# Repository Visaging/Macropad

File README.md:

# Hackpad

## Softwares Used
* Autodesk Fusion
* Kicad 9.0

## BOM
* **Microcontroller** - Seeed Studio XIAO RP2040
* **Switches(x6)** - Cherry MX Compatible Mechanical Switches
* **Keycaps(x6)** - Blank DSA Keycaps
* **RGB LED(x4)** - SK6812MINI Addressable RGB LED(s)
* **OLED Display(x1)** - SSD1306 128x32 OLED Display
* **Bolts:** M3x16 Bolt(x4)
* **Heatset:** M3 Heatset(x4)
* **Case** - 3D printed

## PCB Layout
* **Key Pins:** D0, D1, D3, D6, D7, D8
* **RGB:** D10
* **OLED**: D5, D6, 3V3
* **Power:** VBUS (5V)

## PCB Schematic and Design

## Case Model

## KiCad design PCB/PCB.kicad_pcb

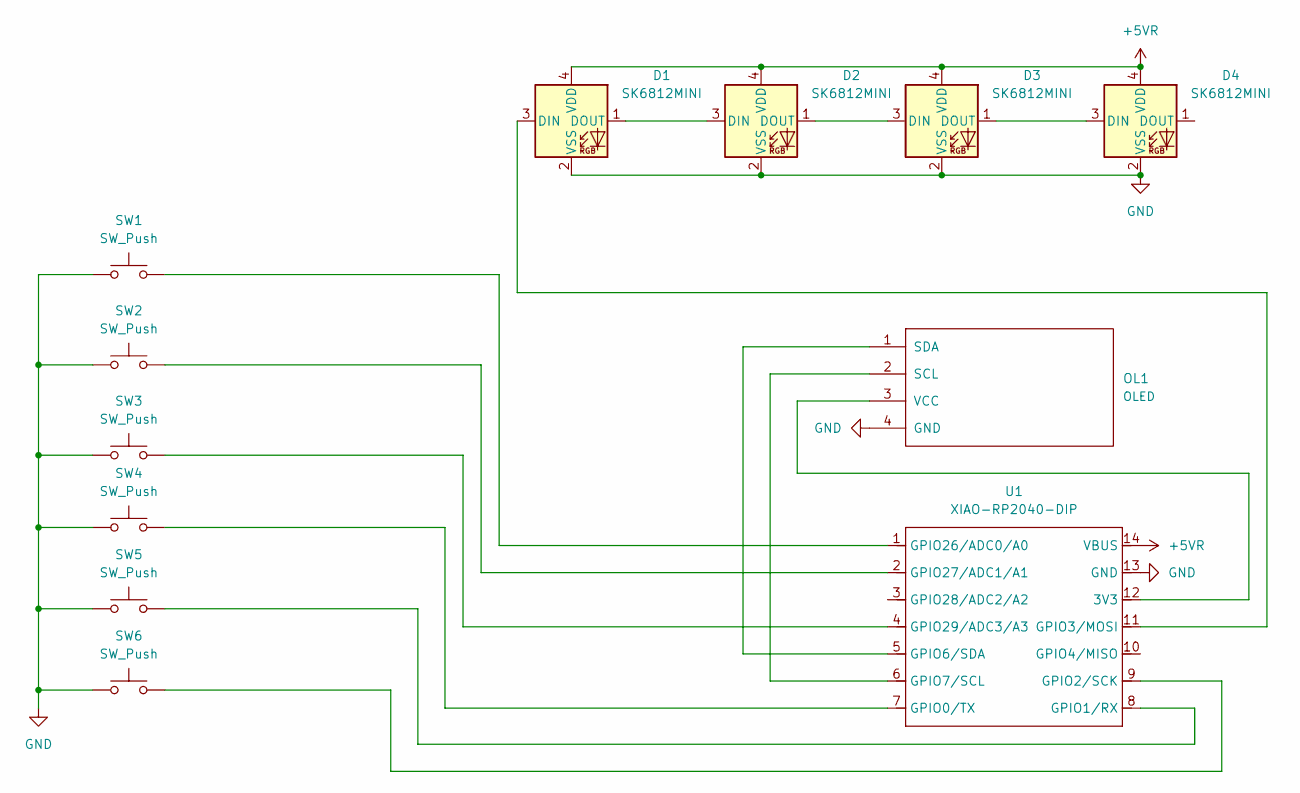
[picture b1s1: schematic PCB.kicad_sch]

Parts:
D1, D2, D3, D4: SK6812MINI; LED_SK6812MINI_PLCC4_3.5x3.5mm_P1.75mm
OL1: OLED
SW1, SW2, SW3, SW4, SW5, SW6: SW_Push; SW_Cherry_MX_1.00u_PCB
U1: XIAO-RP2040-DIP

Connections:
+5VR: D1.4 (VDD), D2.4 (VDD), D3.4 (VDD), D4.4 (VDD), U1.14 (VBUS)
GND: D1.2 (VSS), D2.2 (VSS), D3.2 (VSS), D4.2 (VSS), OL1.4 (GND), SW1.1, SW2.1, SW3.1, SW4.1, SW5.1, SW6.1, U1.13 (GND)
unnamed: D1.3 (DIN), U1.11 (GPIO3/MOSI)
unnamed: D1.1 (DOUT), D2.3 (DIN)
unnamed: D2.1 (DOUT), D3.3 (DIN)
unnamed: D3.1 (DOUT), D4.3 (DIN)
unnamed: OL1.2 (SCL), U1.6 (GPIO7/SCL)
unnamed: OL1.1 (SDA), U1.5 (GPIO6/SDA)
unnamed: OL1.3 (VCC), U1.12 (3V3)
unnamed: SW4.2, U1.7 (GPIO0/TX)
unnamed: SW5.2, U1.8 (GPIO1/RX)
unnamed: SW6.2, U1.9 (GPIO2/SCK)
unnamed: SW1.2, U1.1 (GPIO26/ADC0/A0)
unnamed: SW2.2, U1.2 (GPIO27/ADC1/A1)
unnamed: SW3.2, U1.4 (GPIO29/ADC3/A3)

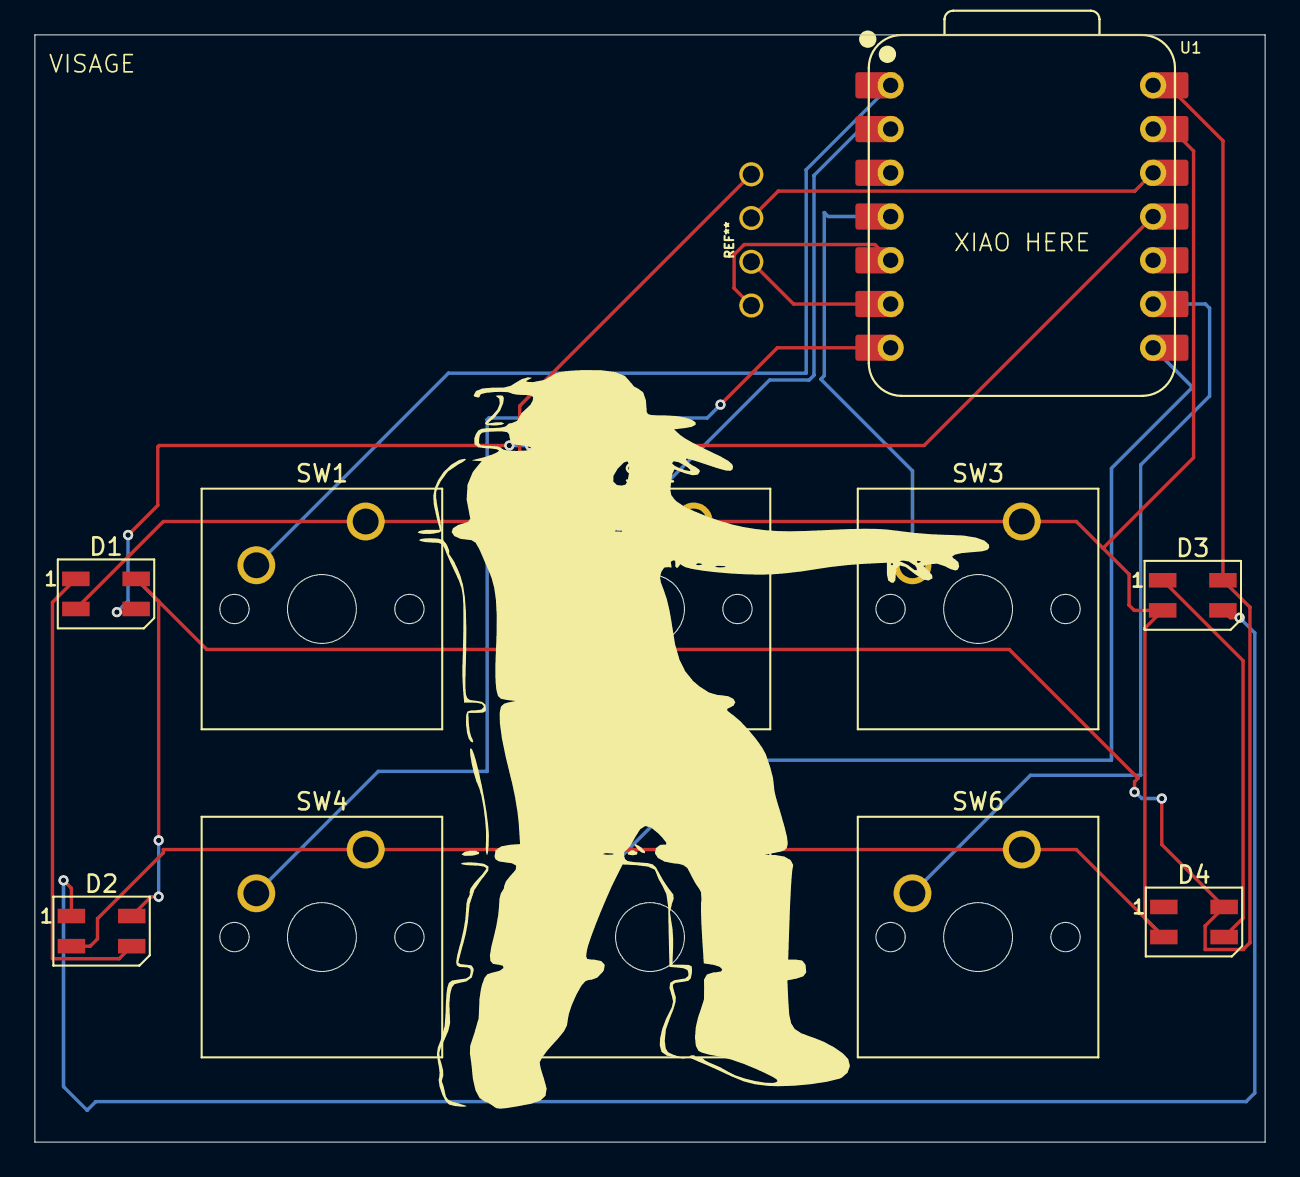
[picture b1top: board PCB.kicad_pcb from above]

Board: 2 copper layers, 71.4 x 64.3 mm, 12 parts (0 on the bottom side), 15 nets.

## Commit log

2026-01-07 Update and rename PCB.kicad_sch to DELETE
